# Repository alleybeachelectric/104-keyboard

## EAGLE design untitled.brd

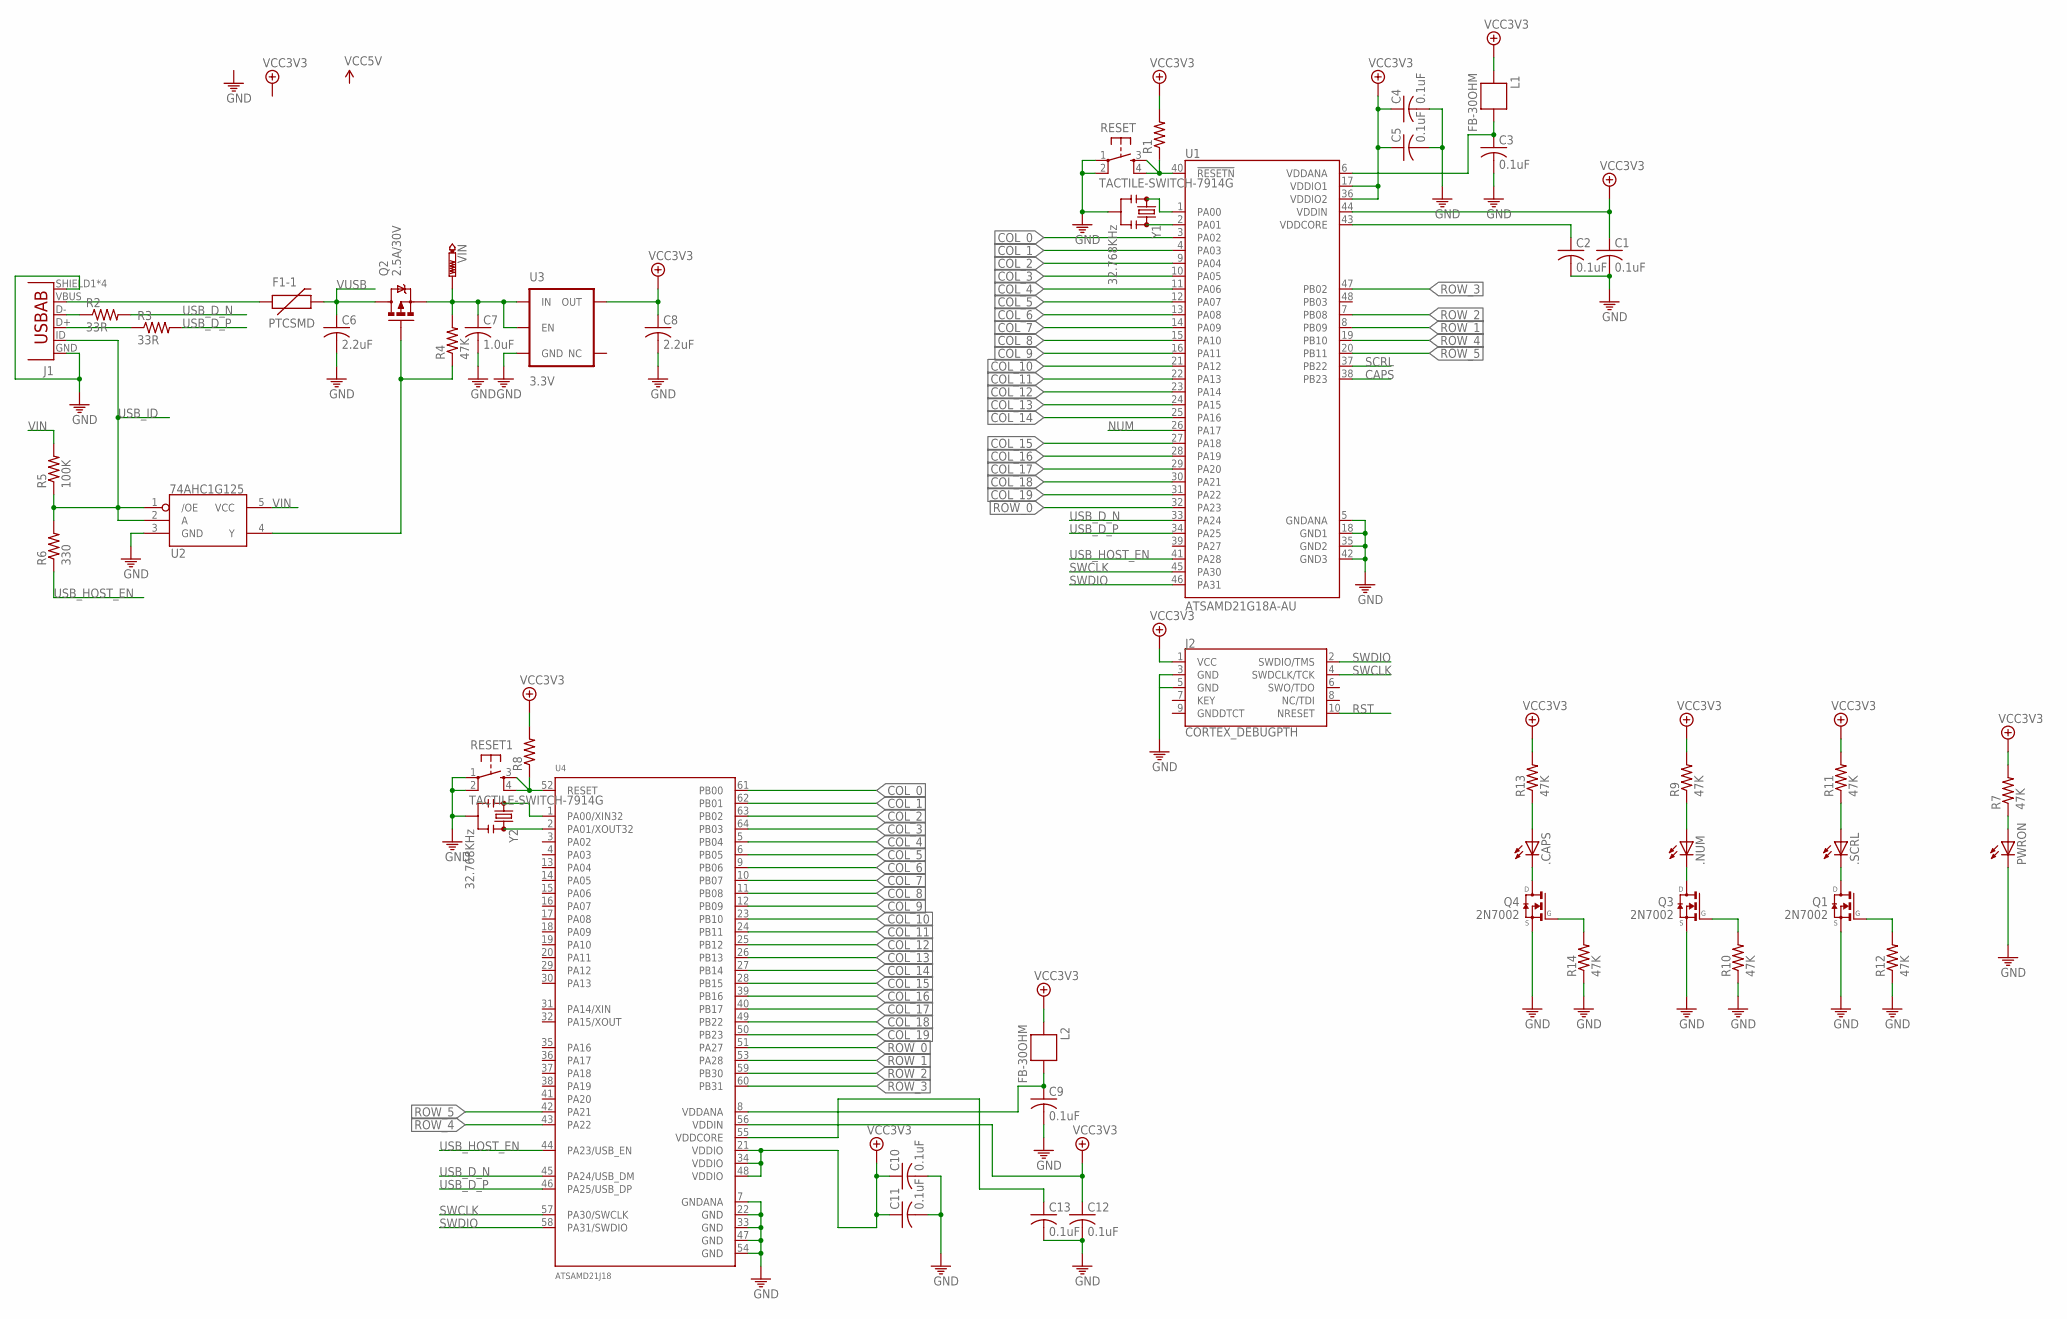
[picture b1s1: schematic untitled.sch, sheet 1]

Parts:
.CAPS, .NUM, .SCRL: LEDCHIPLED_1206; CHIPLED_1206
C1, C2, C3, C4, C5, C9, C10, C11, C12, C13: 0.1uF; C0603
C6, C8: 2.2uF; C0603
C7: 1.0uF; C0603
F1-1: PTCSMD; PTC-1206
J1: USB-AB"; USB_AB_MICRO_1:1_V2
J2: CORTEX_DEBUGPTH; 2X5-PTH-1.27MM
L1, L2: FB-30OHM; 0603
PWRON: LEDCHIPLED_1206; CHIPLED_1206
Q1, Q3, Q4: 2N7002; SOT23
Q2: 2.5A/30V; SOT23-3
R1, R8: R-US_R0603; R0603
R2, R3: 33R; R0603
R4, R7, R9, R10, R11, R12, R13, R14: 47K; R0603
R5: 100K; R0603
R6: 330; R0603
RESET, RESET1: TACTILE-SWITCH-7914G; 7914G
U1: ATSAMD21G18A-AU; QFP50P900X900X120-48N
U2: 74AHC1G125; SOT23-5
U3: 3.3V; SOT23-5
U4: ATSAMD21J18
VIN: PTR1PAD1-17; P1-17
Y1, Y2: 32.768KHz; RESONATOR-SMD

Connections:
CAPS: Q4.1 (G), R14.2, U1.38 (PB23)
COL_0: U1.3 (PA02), U4.61 (PB00); also elsewhere on the board
COL_1: U1.4 (PA03), U4.62 (PB01); also elsewhere on the board
COL_2: U1.9 (PA04), U4.63 (PB02); also elsewhere on the board
COL_3: U1.10 (PA05), U4.64 (PB03); also elsewhere on the board
COL_4: U1.11 (PA06), U4.5 (PB04); also elsewhere on the board
COL_5: U1.12 (PA07), U4.6 (PB05); also elsewhere on the board
COL_6: U1.13 (PA08), U4.9 (PB06); also elsewhere on the board
COL_7: U1.14 (PA09), U4.10 (PB07); also elsewhere on the board
COL_8: U1.15 (PA10), U4.11 (PB08); also elsewhere on the board
COL_9: U1.16 (PA11), U4.12 (PB09); also elsewhere on the board
COL_10: U1.21 (PA12), U4.23 (PB10); also elsewhere on the board
COL_11: U1.22 (PA13), U4.24 (PB11); also elsewhere on the board
COL_12: U1.23 (PA14), U4.25 (PB12); also elsewhere on the board
COL_13: U1.24 (PA15), U4.26 (PB13); also elsewhere on the board
COL_14: U1.25 (PA16), U4.27 (PB14); also elsewhere on the board
COL_15: U1.27 (PA18), U4.28 (PB15); also elsewhere on the board
COL_16: U1.28 (PA19), U4.39 (PB16); also elsewhere on the board
COL_17: U1.29 (PA20), U4.40 (PB17); also elsewhere on the board
COL_18: U1.30 (PA21), U4.49 (PB22); also elsewhere on the board
COL_19: U1.31 (PA22), U4.50 (PB23); also elsewhere on the board
D_N: J1.D-, R2.1
D_P: J1.D+, R3.1
GND: C1.2, C2.2, C3.2, C4.2, C5.2, C6.2, C7.2, C8.2, C9.2, C10.2, C11.2, C12.2, C13.2, J1.GND, J1.SHIELD1 (SHIELD), J1.SHIELD2 (SHIELD), J1.SHIELD3 (SHIELD), J1.SHIELD4 (SHIELD), J2.3 (GND), J2.5 (GND), PWRON.C, Q1.2 (S), Q3.2 (S), Q4.2 (S), R10.1, R12.1, R14.1, RESET.1, RESET.2, RESET1.1, RESET1.2, U1.5 (GNDANA), U1.18 (GND1), U1.35 (GND2), U1.42 (GND3), U2.3 (GND), U3.2 (GND), U4.7 (GNDANA), U4.22 (GND), U4.33 (GND), U4.47 (GND), U4.54 (GND), Y1.2, Y2.2
unnamed: U1.1 (PA00), Y1.1
unnamed: C2.1, U1.43 (VDDCORE)
unnamed: U1.2 (PA01), Y1.3
unnamed: C3.1, L1.1, U1.6 (VDDANA)
unnamed: Q2.1 (G), R4.1, U2.4 (Y)
unnamed: F1-1.1, J1.VBUS
unnamed: PWRON.A, R7.1
unnamed: .SCRL.A, R11.1
unnamed: .NUM.A, R9.1
unnamed: .NUM.C, Q3.3 (D)
unnamed: .SCRL.C, Q1.3 (D)
unnamed: U4.1 (PA00/XIN32), Y2.1
unnamed: U4.2 (PA01/XOUT32), Y2.3
unnamed: C9.1, L2.1, U4.8 (VDDANA)
unnamed: C13.1, U4.55 (VDDCORE)
unnamed: .CAPS.A, R13.1
unnamed: .CAPS.C, Q4.3 (D)
NUM: Q3.1 (G), R10.2, U1.26 (PA17)
ROW_0: U1.32 (PA23), U4.51 (PA27); also elsewhere on the board
ROW_1: U1.8 (PB09), U4.53 (PA28); also elsewhere on the board
ROW_2: U1.7 (PB08), U4.59 (PB30); also elsewhere on the board
ROW_3: U1.47 (PB02), U4.60 (PB31); also elsewhere on the board
ROW_4: U1.19 (PB10), U4.43 (PA22); also elsewhere on the board
ROW_5: U1.20 (PB11), U4.42 (PA21); also elsewhere on the board
RST: J2.10 (NRESET), R1.1, RESET.3, RESET.4, U1.40 (!RESETN)
RST1: R8.1, RESET1.3, RESET1.4, U4.52 (RESET)
SCRL: Q1.1 (G), R12.2, U1.37 (PB22)
SWCLK: J2.4 (SWDCLK/TCK), U1.45 (PA30), U4.57 (PA30/SWCLK)
SWDIO: J2.2 (SWDIO/TMS), U1.46 (PA31), U4.58 (PA31/SWDIO)
USB_D_N: R2.2, U1.33 (PA24), U4.45 (PA24/USB_DM)
USB_D_P: R3.2, U1.34 (PA25), U4.46 (PA25/USB_DP)
USB_HOST_EN: R6.1, U1.41 (PA28)
USB_ID: J1.ID (USBID), R5.1, R6.2, U2.1 (/OE), U2.2 (A)
VCC3V3: C1.1, C4.1, C5.1, C8.1, C10.1, C11.1, C12.1, J2.1 (VCC), L1.2, L2.2, R1.2, R7.2, R8.2, R9.2, R11.2, R13.2, U1.17 (VDDIO1), U1.36 (VDDIO2), U1.44 (VDDIN), U3.5 (OUT), U4.21 (VDDIO), U4.34 (VDDIO), U4.48 (VDDIO), U4.56 (VDDIN)
VIN: C7.1, Q2.2 (S), R4.2, R5.2, U2.5 (VCC), U3.1 (IN), U3.3 (EN), VIN.TP
VUSB: C6.1, F1-1.2, Q2.3 (D)

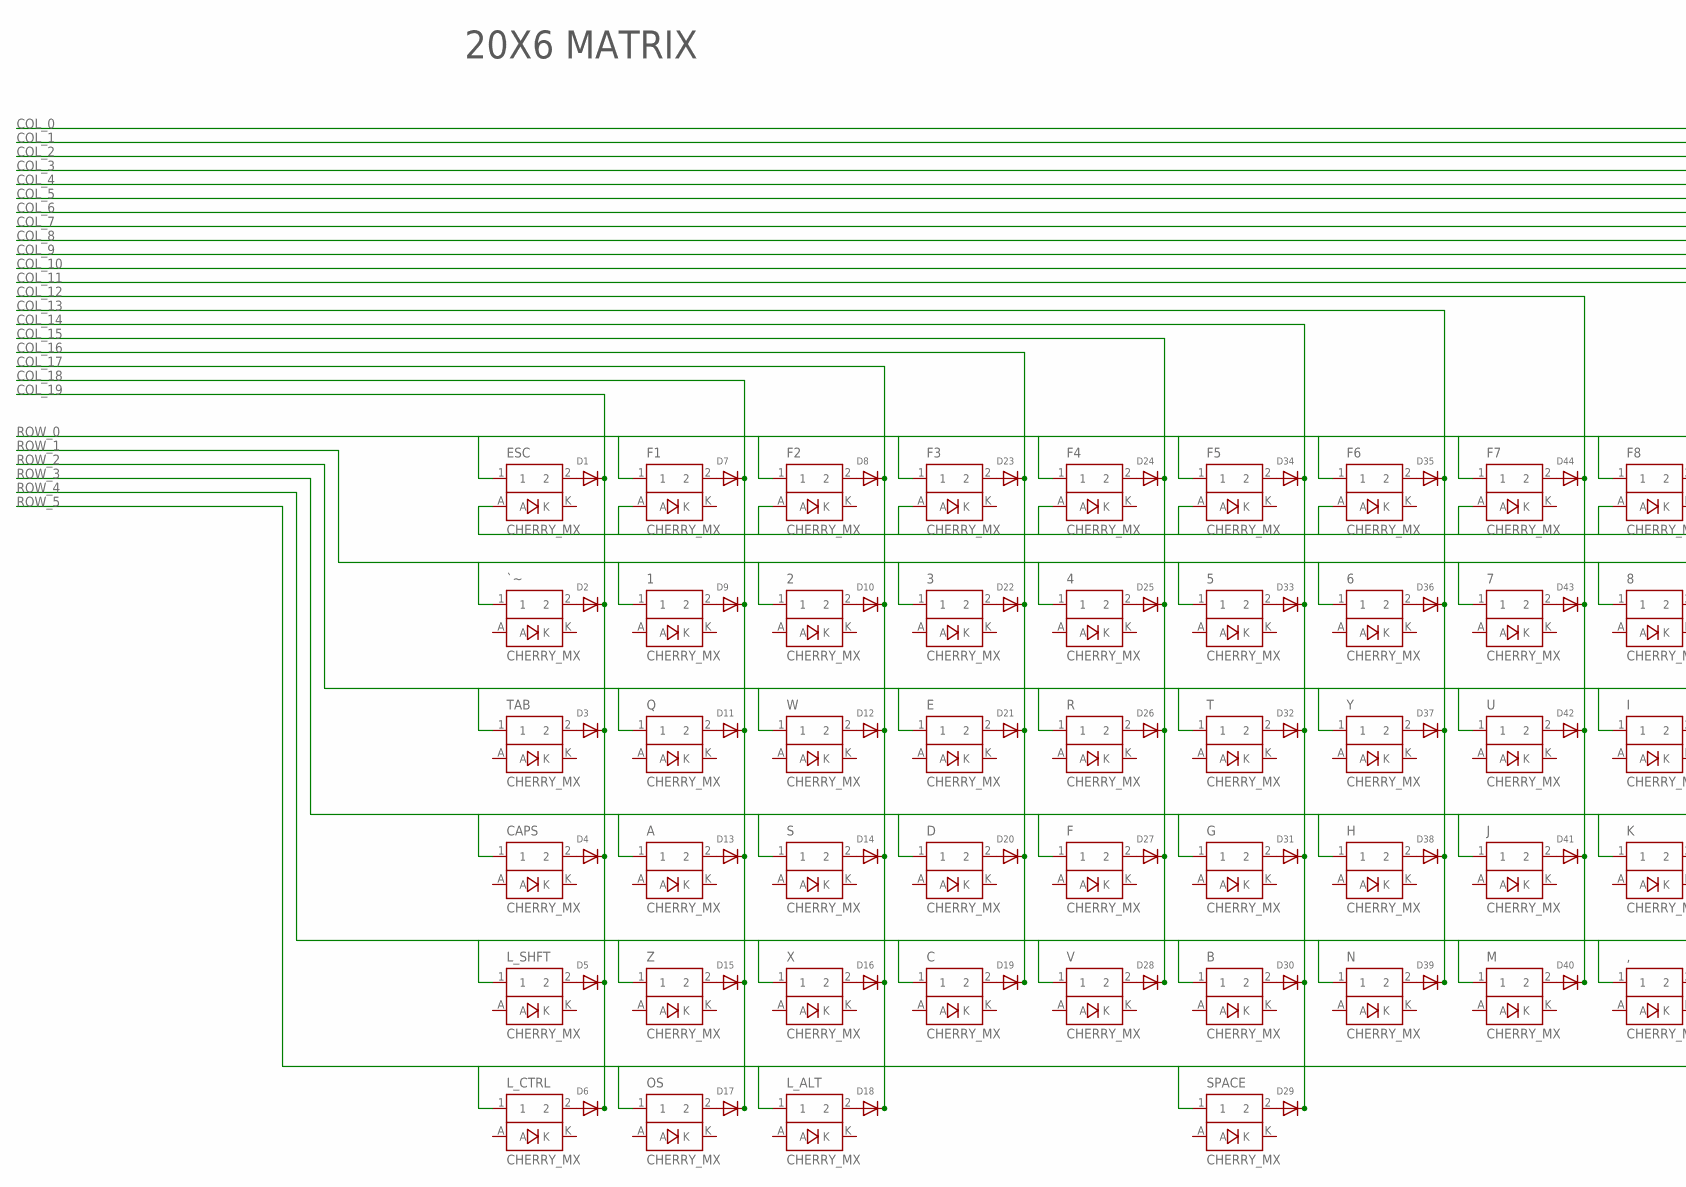
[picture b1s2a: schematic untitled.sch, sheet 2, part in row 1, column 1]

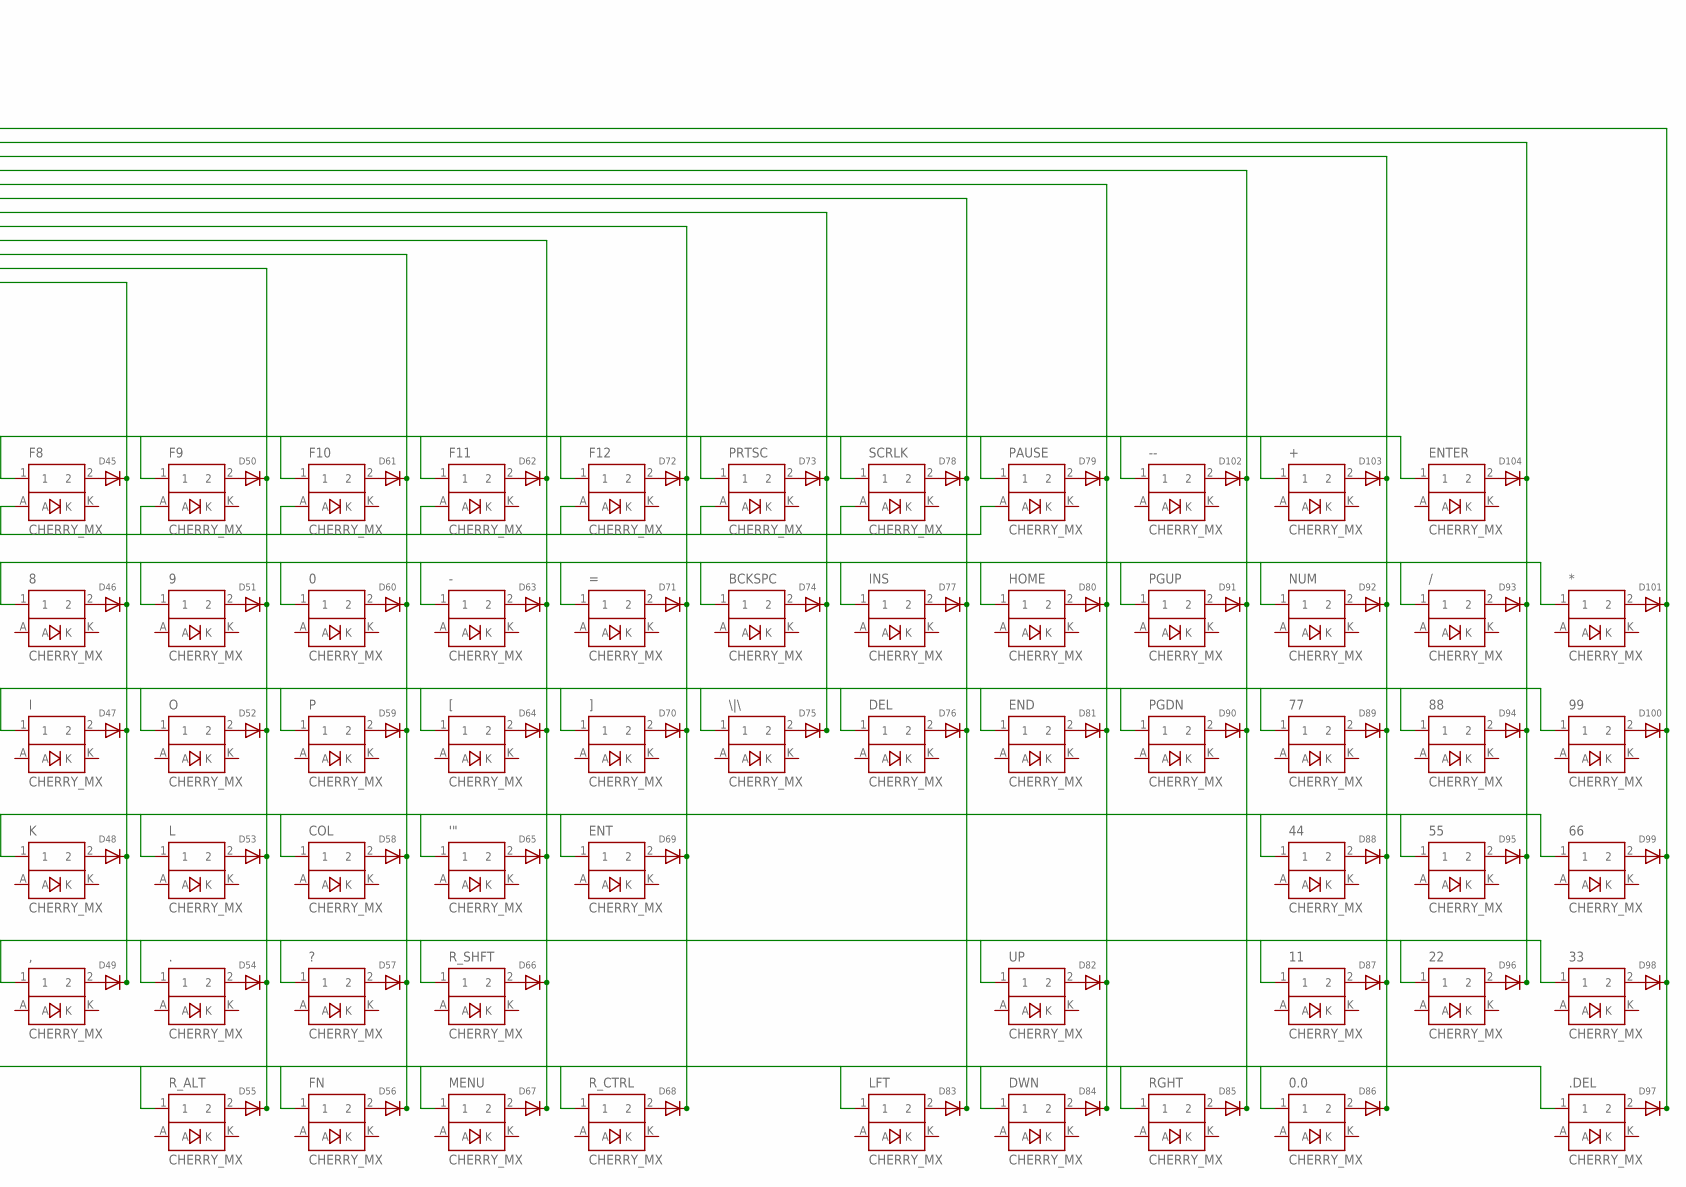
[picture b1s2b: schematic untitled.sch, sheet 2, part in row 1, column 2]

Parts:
0, 0.0, 1, 2, 3, 4, 5, 6, 7, 8, 9, 11, 22, 33, 44, 55, 66, 77, 88, 99, ., .DEL: CHERRY_MX
'": CHERRY_MX
*: CHERRY_MX
+: CHERRY_MX
,: CHERRY_MX
-: CHERRY_MX
--: CHERRY_MX
/: CHERRY_MX
=: CHERRY_MX
?: CHERRY_MX
A: CHERRY_MX
B: CHERRY_MX
BCKSPC: CHERRY_MX
C: CHERRY_MX
CAPS: CHERRY_MX
COL: CHERRY_MX
D: CHERRY_MX
D1, D2, D3, D4, D5, D6, D7, D8, D9, D10, D11, D12, D13, D14, D15, D16, D17, D18, D19, D20, D21, D22, D23, D24, D25, D26, D27, D28, D29, D30, D31, D32, D33, D34, D35, D36, D37, D38, D39, D40, D41, D42, D43, D44, D45, D46, D47, D48, D49, D50, D51, D52, D53, D54, D55, D56, D57, D58, D59, D60, D61, D62, D63, D64, D65, D66, D67, D68, D69, D70, D71, D72, D73, D74, D75, D76, D77, D78, D79, D80, D81, D82, D83, D84, D85, D86, D87, D88, D89, D90, D91, D92, D93, D94, D95, D96, D97, D98, D99, D100, D101, D102, D103, D104: DIODESOD-323F; SOD-323F
DEL: CHERRY_MX
DWN: CHERRY_MX
E: CHERRY_MX
END: CHERRY_MX
ENT: CHERRY_MX
ENTER: CHERRY_MX
ESC: CHERRY_MX
F, F1, F2, F3, F4, F5, F6, F7, F8, F9, F10, F11, F12: CHERRY_MX
FN: CHERRY_MX
G: CHERRY_MX
H: CHERRY_MX
HOME: CHERRY_MX
I: CHERRY_MX
INS: CHERRY_MX
J: CHERRY_MX
K: CHERRY_MX
L: CHERRY_MX
LFT: CHERRY_MX
L_ALT: CHERRY_MX
L_CTRL: CHERRY_MX
L_SHFT: CHERRY_MX
M: CHERRY_MX
MENU: CHERRY_MX
N: CHERRY_MX
NUM: CHERRY_MX
O: CHERRY_MX
OS: CHERRY_MX
P: CHERRY_MX
PAUSE: CHERRY_MX
PGDN: CHERRY_MX
PGUP: CHERRY_MX
PRTSC: CHERRY_MX
Q: CHERRY_MX
R: CHERRY_MX
RGHT: CHERRY_MX
R_ALT: CHERRY_MX
R_CTRL: CHERRY_MX
R_SHFT: CHERRY_MX
S: CHERRY_MX
SCRLK: CHERRY_MX
SPACE: CHERRY_MX
T: CHERRY_MX
TAB: CHERRY_MX
U: CHERRY_MX
UP: CHERRY_MX
V: CHERRY_MX
W: CHERRY_MX
X: CHERRY_MX
Y: CHERRY_MX
Z: CHERRY_MX
[: CHERRY_MX
\|\: CHERRY_MX
]: CHERRY_MX
`~: CHERRY_MX

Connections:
COL_0: D97.C, D98.C, D99.C, D100.C, D101.C; also elsewhere on the board
COL_1: D93.C, D94.C, D95.C, D96.C, D104.C; also elsewhere on the board
COL_2: D86.C, D87.C, D88.C, D89.C, D92.C, D103.C; also elsewhere on the board
COL_3: D85.C, D90.C, D91.C, D102.C; also elsewhere on the board
COL_4: D79.C, D80.C, D81.C, D82.C, D84.C; also elsewhere on the board
COL_5: D76.C, D77.C, D78.C, D83.C; also elsewhere on the board
COL_6: D73.C, D74.C, D75.C; also elsewhere on the board
COL_7: D68.C, D69.C, D70.C, D71.C, D72.C; also elsewhere on the board
COL_8: D62.C, D63.C, D64.C, D65.C, D66.C, D67.C; also elsewhere on the board
COL_9: D56.C, D57.C, D58.C, D59.C, D60.C, D61.C; also elsewhere on the board
COL_10: D50.C, D51.C, D52.C, D53.C, D54.C, D55.C; also elsewhere on the board
COL_11: D45.C, D46.C, D47.C, D48.C, D49.C; also elsewhere on the board
COL_12: D40.C, D41.C, D42.C, D43.C, D44.C; also elsewhere on the board
COL_13: D35.C, D36.C, D37.C, D38.C, D39.C; also elsewhere on the board
COL_14: D29.C, D30.C, D31.C, D32.C, D33.C, D34.C; also elsewhere on the board
COL_15: D24.C, D25.C, D26.C, D27.C, D28.C; also elsewhere on the board
COL_16: D19.C, D20.C, D21.C, D22.C, D23.C; also elsewhere on the board
COL_17: D8.C, D10.C, D12.C, D14.C, D16.C, D18.C; also elsewhere on the board
COL_18: D7.C, D9.C, D11.C, D13.C, D15.C, D17.C; also elsewhere on the board
COL_19: D1.C, D2.C, D3.C, D4.C, D5.C, D6.C; also elsewhere on the board
unnamed: D1.A, ESC.2
unnamed: ESC.A, F1.A, F2.A, F3.A, F4.A, F5.A, F6.A, F7.A, F8.A, F9.A, F10.A, F11.A, F12.A, PAUSE.A, PRTSC.A, SCRLK.A
unnamed: D7.A, F1.2
unnamed: D2.A, `~.2
unnamed: D3.A, TAB.2
unnamed: CAPS.2, D4.A
unnamed: D5.A, L_SHFT.2
unnamed: D6.A, L_CTRL.2
unnamed: D8.A, F2.2
unnamed: 1.2, D9.A
unnamed: 2.2, D10.A
unnamed: D11.A, Q.2
unnamed: D12.A, W.2
unnamed: A.2, D13.A
unnamed: D14.A, S.2
unnamed: D15.A, Z.2
unnamed: D16.A, X.2
unnamed: D17.A, OS.2
unnamed: D18.A, L_ALT.2
unnamed: C.2, D19.A
unnamed: D.2, D20.A
unnamed: D21.A, E.2
unnamed: 3.2, D22.A
unnamed: D23.A, F3.2
unnamed: D24.A, F4.2
unnamed: 4.2, D25.A
unnamed: D26.A, R.2
unnamed: D27.A, F.2
unnamed: D28.A, V.2
unnamed: D29.A, SPACE.2
unnamed: B.2, D30.A
unnamed: D31.A, G.2
unnamed: D32.A, T.2
unnamed: 5.2, D33.A
unnamed: D34.A, F5.2
unnamed: D35.A, F6.2
unnamed: 6.2, D36.A
unnamed: D37.A, Y.2
unnamed: D38.A, H.2
unnamed: D39.A, N.2
unnamed: D40.A, M.2
unnamed: D41.A, J.2
unnamed: D42.A, U.2
unnamed: 7.2, D43.A
unnamed: D44.A, F7.2
unnamed: D45.A, F8.2
unnamed: 8.2, D46.A
unnamed: D47.A, I.2
unnamed: D48.A, K.2
unnamed: ,.2, D49.A
unnamed: D50.A, F9.2
unnamed: 9.2, D51.A
unnamed: D52.A, O.2
unnamed: D53.A, L.2
unnamed: ..2, D54.A
unnamed: D55.A, R_ALT.2
unnamed: D56.A, FN.2
unnamed: ?.2, D57.A
unnamed: COL.2, D58.A
unnamed: D59.A, P.2
unnamed: 0.2, D60.A
unnamed: D61.A, F10.2
unnamed: D62.A, F11.2
unnamed: -.2, D63.A
unnamed: D64.A, [.2
unnamed: '".2, D65.A
unnamed: D66.A, R_SHFT.2
unnamed: D67.A, MENU.2
unnamed: D68.A, R_CTRL.2
unnamed: D69.A, ENT.2
unnamed: D70.A, ].2
unnamed: =.2, D71.A
unnamed: D72.A, F12.2
unnamed: D73.A, PRTSC.2
unnamed: BCKSPC.2, D74.A
unnamed: D75.A, \|\.2
unnamed: D76.A, DEL.2
unnamed: D77.A, INS.2
unnamed: D78.A, SCRLK.2
unnamed: D79.A, PAUSE.2
unnamed: D80.A, HOME.2
unnamed: D81.A, END.2
unnamed: D82.A, UP.2
unnamed: D83.A, LFT.2
unnamed: D84.A, DWN.2
unnamed: D85.A, RGHT.2
unnamed: 0.0.2, D86.A
unnamed: 11.2, D87.A
unnamed: 44.2, D88.A
unnamed: 77.2, D89.A
unnamed: D90.A, PGDN.2
unnamed: D91.A, PGUP.2
unnamed: D92.A, NUM.2
unnamed: /.2, D93.A
unnamed: 88.2, D94.A
unnamed: 55.2, D95.A
unnamed: 22.2, D96.A
unnamed: .DEL.2, D97.A
unnamed: 33.2, D98.A
unnamed: 66.2, D99.A
unnamed: 99.2, D100.A
unnamed: *.2, D101.A
unnamed: --.2, D102.A
unnamed: D104.A, ENTER.2
unnamed: +.2, D103.A
ROW_0: +.1, --.1, ENTER.1, ESC.1, F1.1, F2.1, F3.1, F4.1, F5.1, F6.1, F7.1, F8.1, F9.1, F10.1, F11.1, F12.1, PAUSE.1, PRTSC.1, SCRLK.1; also elsewhere on the board
ROW_1: 0.1, 1.1, 2.1, 3.1, 4.1, 5.1, 6.1, 7.1, 8.1, 9.1, *.1, -.1, /.1, =.1, BCKSPC.1, HOME.1, INS.1, NUM.1, PGUP.1, `~.1; also elsewhere on the board
ROW_2: 77.1, 88.1, 99.1, DEL.1, E.1, END.1, I.1, O.1, P.1, PGDN.1, Q.1, R.1, T.1, TAB.1, U.1, W.1, Y.1, [.1, \|\.1, ].1; also elsewhere on the board
ROW_3: 44.1, 55.1, 66.1, '".1, A.1, CAPS.1, COL.1, D.1, ENT.1, F.1, G.1, H.1, J.1, K.1, L.1, S.1; also elsewhere on the board
ROW_4: 11.1, 22.1, 33.1, ,.1, ..1, ?.1, B.1, C.1, L_SHFT.1, M.1, N.1, R_SHFT.1, UP.1, V.1, X.1, Z.1; also elsewhere on the board
ROW_5: 0.0.1, .DEL.1, DWN.1, FN.1, LFT.1, L_ALT.1, L_CTRL.1, MENU.1, OS.1, RGHT.1, R_ALT.1, R_CTRL.1, SPACE.1; also elsewhere on the board

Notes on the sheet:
20X6 MATRIX

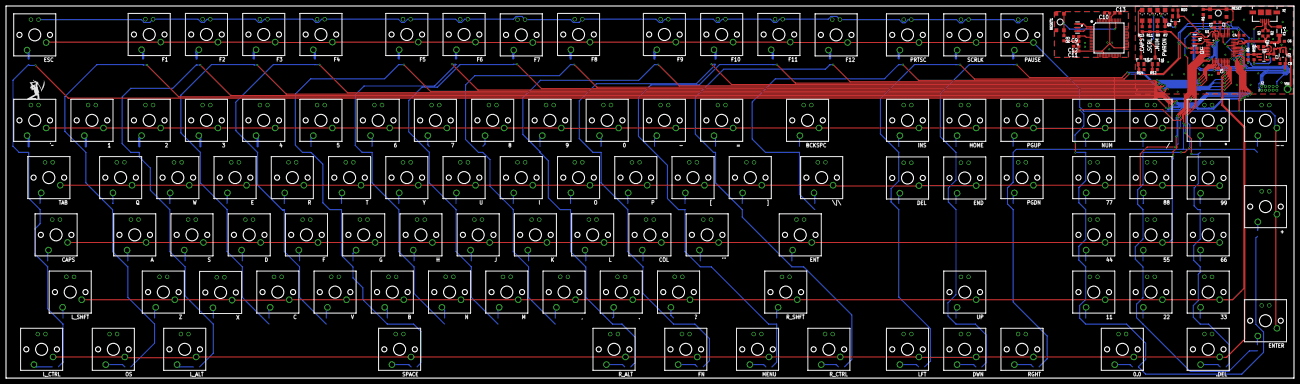
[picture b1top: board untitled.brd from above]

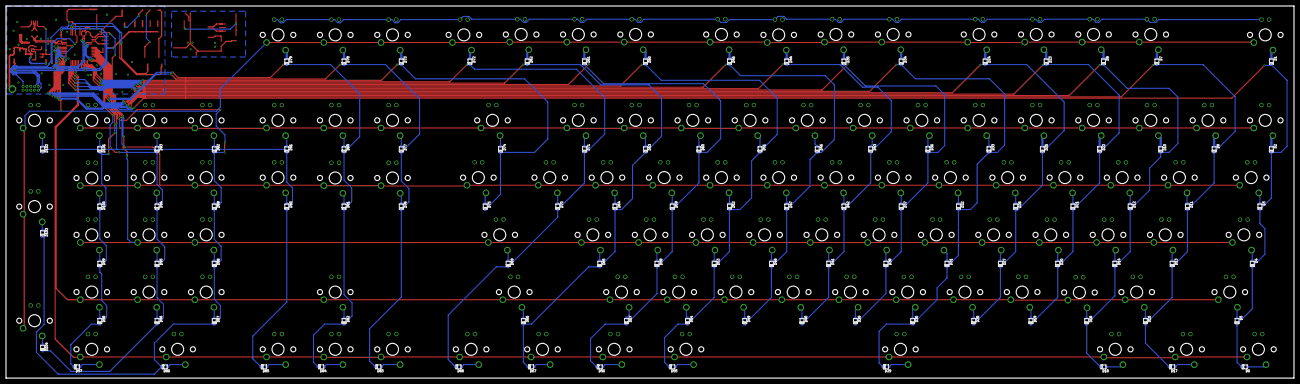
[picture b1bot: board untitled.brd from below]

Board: 2 copper layers, 428.6 x 123.8 mm, 257 parts (104 on the bottom side), 165 nets.

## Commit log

2017-03-21 initial commit.

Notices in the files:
parts and their libraries:
SparkFun-Passives: Licensing: Creative Commons ShareAlike 4.0 International - https://creativecommons.org/licenses/by-sa/4.0
